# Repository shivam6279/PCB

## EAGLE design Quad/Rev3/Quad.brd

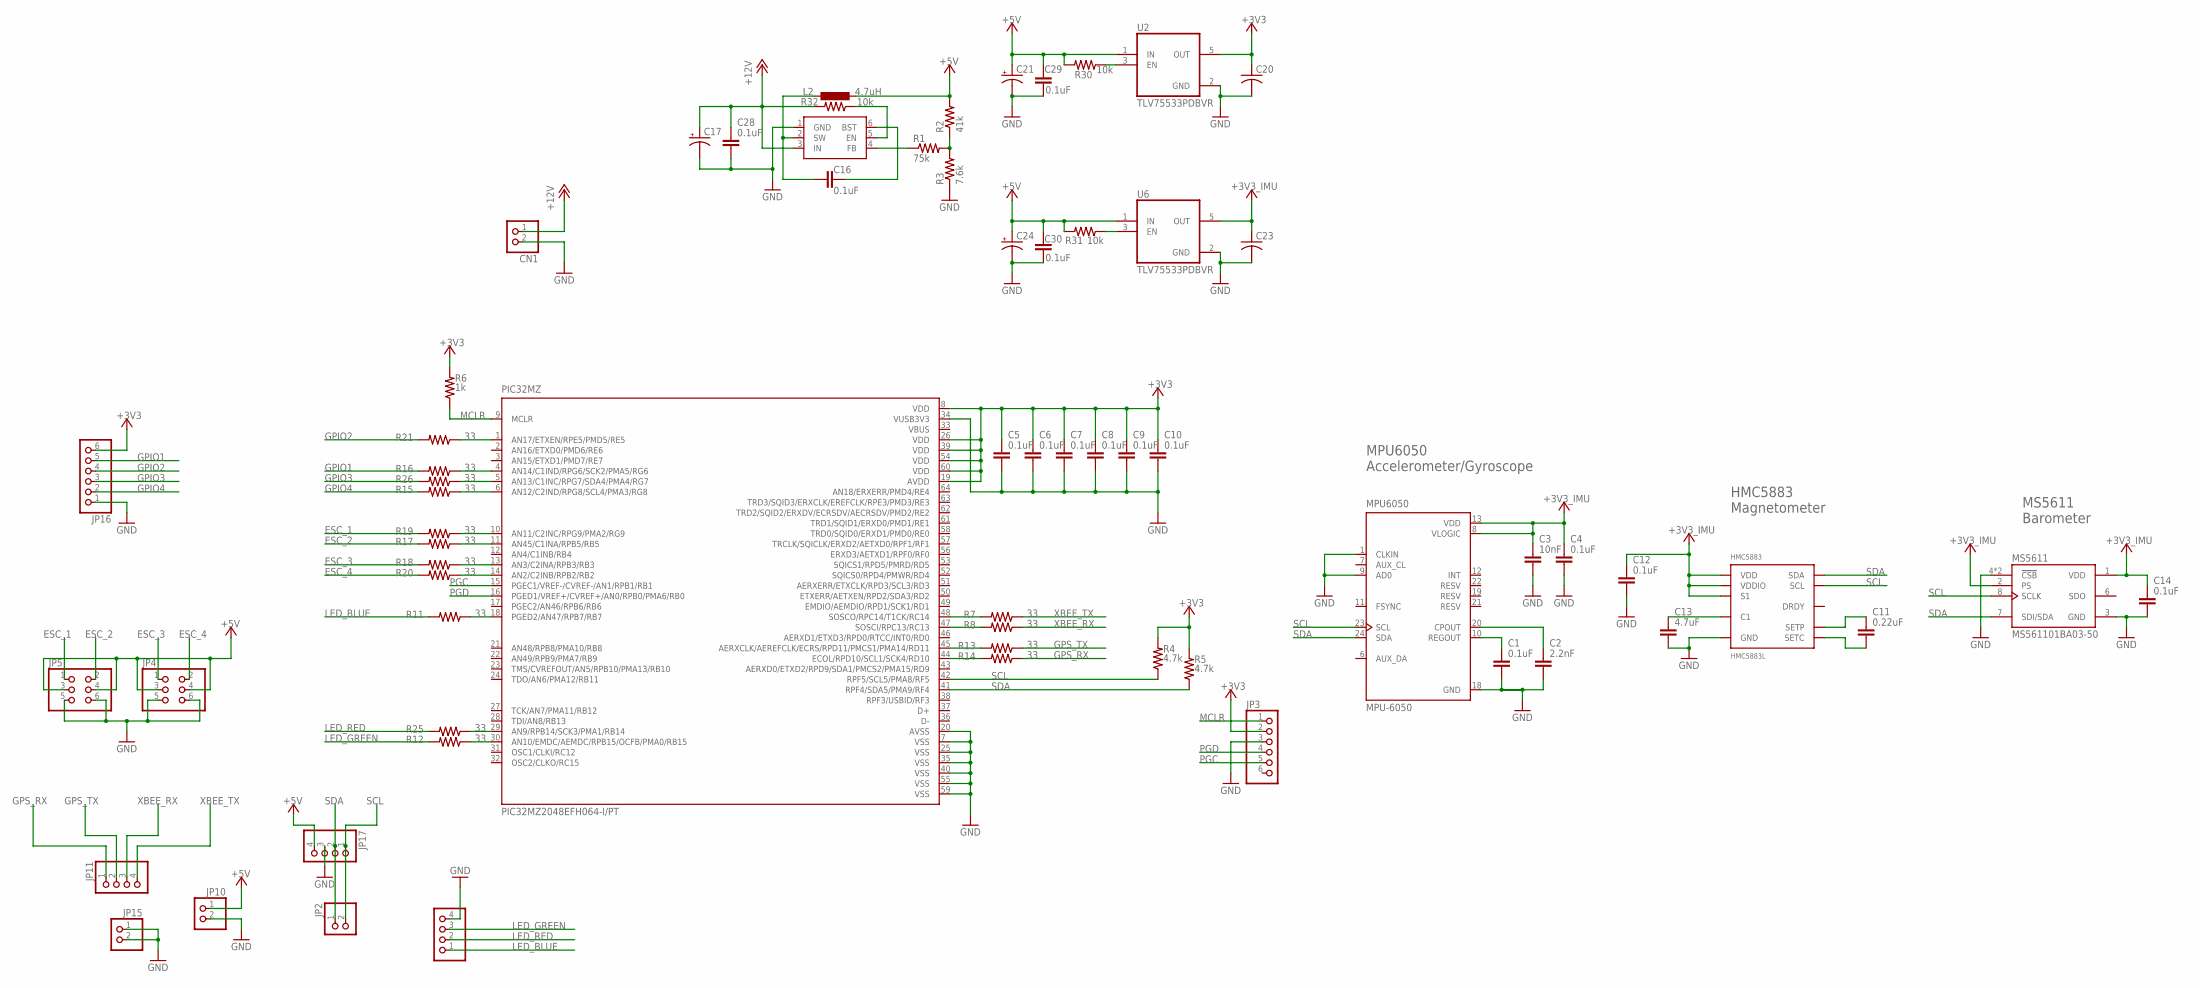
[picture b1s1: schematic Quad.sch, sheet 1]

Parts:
C1, C4, C5, C6, C7, C8, C9, C10, C12, C14, C16, C28, C29, C30: 0.1uF; C0603
C2: 2.2nF; C0603
C3: 10nF; C0603
C11: 0.22uF; C0603
C13: 4.7uF; C0603
C17: CPOL-USC/6032-28R; C/6032-28R
C20, C23: C-USC0805; C0805
C21, C24: CPOL-USB/3528-21W; B/3528-21W
CN1: JST_2PIN-THM-RA; JST-PH-2-THM-RA
HMC5883: HMC5883L; LPCC-16
JP2, JP10, JP15: PINHD-1X2; 1X02
JP3: PINHD-1X6/90; 1X06/90
JP4, JP5: PINHD-2X3; 2X03
JP9, JP11: PINHD-1X4; 1X04
JP16: PINHD-1X6; 1X06
JP17: PINHD-1X4/90; 1X04/90
L2: 4.7uH; L2825P
MPU6050: MPU-6050; QFN50P400X400X95-24N
MS5611: MS561101BA03-50; SON125P500X300X100-8N
PIC32MZ: PIC32MZ2048EFH064-I/PT; QFP50P1200X1200X120-64N
R1: 75k; R0603
R2: 41k; R0603
R3: 7.6k; R0603
R4, R5: 4.7k; R0603
R6: 1k; R0603
R7, R8, R11, R12, R13, R14, R15, R16, R17, R18, R19, R20, R21, R25, R26: 33; R0603
R30, R31, R32: 10k; R0603
U2, U6: TLV75533PDBVR; SOT95P280X145-5N
U$2: AP65211A; SOT95P280X140-6N

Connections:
+3V3: C5.1, C6.1, C7.1, C8.1, C9.1, C10.1, C20.1, JP3.2, JP16.6, PIC32MZ.8 (VDD), PIC32MZ.19 (AVDD), PIC32MZ.26 (VDD), PIC32MZ.39 (VDD), PIC32MZ.54 (VDD), PIC32MZ.60 (VDD), R4.2, R5.2, R6.2, U2.5 (OUT)
+5V: C21.+, C24.+, C29.1, C30.1, JP4.3, JP4.4, JP5.3, JP5.4, JP10.1, JP17.4, L2.1, R2.2, R30.2, R31.2, U2.1 (IN), U6.1 (IN)
+12V: C17.+, C28.1, CN1.1 (2), R32.2, U$2.3 (IN)
ESC_1: JP5.1, R19.2
ESC_2: JP5.2, R17.2
ESC_3: JP4.1, R18.2
ESC_4: JP4.2, R20.2
GND: C1.2, C2.2, C3.2, C4.2, C5.2, C6.2, C7.2, C8.2, C9.2, C10.2, C12.2, C13.2, C14.2, C17.-, C20.2, C21.-, C23.2, C24.-, C28.2, C29.2, C30.2, CN1.2 (1), HMC5883.9 (GND), HMC5883.11 (GND), JP3.3, JP4.5, JP4.6, JP5.5, JP5.6, JP9.4, JP10.2, JP15.1, JP15.2, JP16.1, JP17.3, MPU6050.1 (CLKIN), MPU6050.9 (AD0), MPU6050.18 (GND), MS5611.3 (GND), MS5611.4 (!CSB), MS5611.5 (!CSB), PIC32MZ.7 (VSS), PIC32MZ.20 (AVSS), PIC32MZ.25 (VSS), PIC32MZ.34 (VUSB3V3), PIC32MZ.35 (VSS), PIC32MZ.40 (VSS), PIC32MZ.55 (VSS), PIC32MZ.59 (VSS), R3.1, U2.2 (GND), U6.2 (GND), U$2.1 (GND)
GPIO1: JP16.5, R16.2
GPIO2: JP16.4, R21.2
GPIO3: JP16.3, R26.2
GPIO4: JP16.2, R15.2
GPS_RX: JP11.1, R14.1
GPS_TX: JP11.2, R13.1
LED_BLUE: JP9.1, R11.2
LED_GREEN: JP9.3, R12.2
LED_RED: JP9.2, R25.2
MCLR: JP3.1, PIC32MZ.9 (MCLR), R6.1
unnamed: C1.1, MPU6050.10 (REGOUT)
unnamed: C2.1, MPU6050.20 (CPOUT)
unnamed: C11.1, HMC5883.8 (SETP)
unnamed: C11.2, HMC5883.12 (SETC)
unnamed: C13.1, HMC5883.10 (C1)
unnamed: C16.1, L2.2, U$2.2 (SW)
unnamed: C16.2, U$2.6 (BST)
unnamed: R1.1, U$2.4 (FB)
unnamed: R1.2, R2.1, R3.2
unnamed: PIC32MZ.48 (SOSCO/RPC14/T1CK/RC14), R7.2
unnamed: PIC32MZ.47 (SOSCI/RPC13/RC13), R8.2
unnamed: PIC32MZ.18 (PGED2/AN47/RPB7/RB7), R11.1
unnamed: PIC32MZ.45 (AERXCLK/AEREFCLK/ECRS/RPD11/PMCS1/PMA14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), R13.2
unnamed: PIC32MZ.44 (ECOL/RPD10/SCL1/SCK4/RD10), R14.2
unnamed: PIC32MZ.29 (AN9/RPB14/SCK3/PMA1/RB14), R25.1
unnamed: PIC32MZ.4 (AN14/C1IND/RPG6/SCK2/PMA5/RG6), R16.1
unnamed: PIC32MZ.1 (AN17/ETXEN/RPE5/PMD5/RE5), R21.1
unnamed: PIC32MZ.11 (AN45/C1INA/RPB5/RB5), R17.1
unnamed: PIC32MZ.13 (AN3/C2INA/RPB3/RB3), R18.1
unnamed: PIC32MZ.10 (AN11/C2INC/RPG9/PMA2/RG9), R19.1
unnamed: PIC32MZ.14 (AN2/C2INB/RPB2/RB2), R20.1
unnamed: PIC32MZ.5 (AN13/C1INC/RPG7/SDA4/PMA4/RG7), R26.1
unnamed: PIC32MZ.6 (AN12/C2IND/RPG8/SCL4/PMA3/RG8), R15.1
unnamed: R31.1, U6.3 (EN)
unnamed: R30.1, U2.3 (EN)
unnamed: PIC32MZ.30 (AN10/EMDC/AEMDC/RPB15/OCFB/PMA0/RB15), R12.1
unnamed: R32.1, U$2.5 (EN)
PGC: JP3.5, PIC32MZ.15 (PGEC1/VREF-/CVREF-/AN1/RPB1/RB1)
PGD: JP3.4, PIC32MZ.16 (PGED1/VREF+/CVREF+/AN0/RPB0/PMA6/RB0)
SCL: HMC5883.1 (SCL), JP2.2, JP17.1, MPU6050.23 (SCL), MS5611.8 (SCLK), PIC32MZ.42 (RPF5/SCL5/PMA8/RF5), R4.1
SDA: HMC5883.16 (SDA), JP2.1, JP17.2, MPU6050.24 (SDA), MS5611.7 (SDI/SDA), PIC32MZ.41 (RPF4/SDA5/PMA9/RF4), R5.1
VBUS: PIC32MZ.33 (VBUS)
VCC: C3.1, C4.1, C12.1, C14.1, C23.1, HMC5883.2 (VDD), HMC5883.4 (S1), HMC5883.13 (VDDIO), MPU6050.8 (VLOGIC), MPU6050.13 (VDD), MS5611.1 (VDD), MS5611.2 (PS), U6.5 (OUT)
XBEE_RX: JP11.3, R8.1
XBEE_TX: JP11.4, R7.1

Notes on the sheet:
MPU6050 Accelerometer/Gyroscope
HMC5883 Magnetometer
MS5611 Barometer

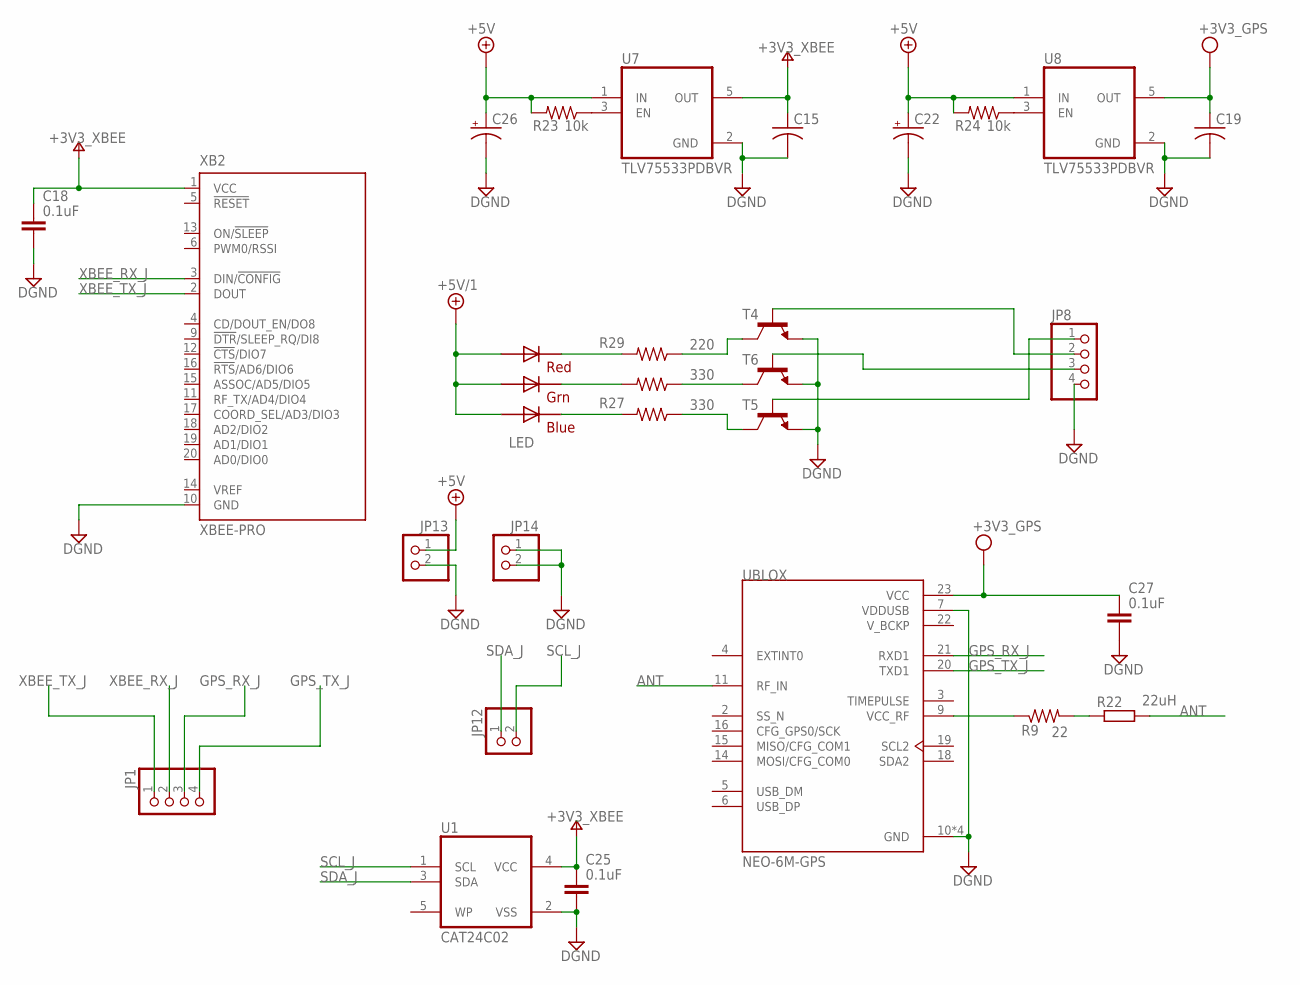
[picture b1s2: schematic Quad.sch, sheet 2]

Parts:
C15, C19: C-USC0805; C0805
C18, C25, C27: 0.1uF; C0603
C22, C26: CPOL-USB/3528-21W; B/3528-21W
JP1, JP8: PINHD-1X4; 1X04
JP12, JP13, JP14: PINHD-1X2; 1X02
LED: RGBLED5050
R9: 22; R0603
R22: 22uH; R0805
R23, R24: 10k; R0603
R27, R28: 330; R0603
R29: 220; R0603
T4, T5, T6: -NPN-SOT23-EBC; SOT23-EBC
U1: CAT24C02; SOT95P280X145-5N
U7, U8: TLV75533PDBVR; SOT95P280X145-5N
UBLOX: NEO-6M-GPS; XCVR_NEO-6M-GPS
XB2: XBEE-PRO

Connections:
+5V/1: C22.+, C26.+, JP13.1, LED.1 (GREEN_A), LED.2 (RED_A), LED.3 (BLUE_A), R23.2, R24.2, U7.1 (IN), U8.1 (IN)
ANT: R22.2, UBLOX.11 (RF_IN)
DGND: C15.2, C18.2, C19.2, C22.-, C25.2, C26.-, C27.2, JP8.4, JP13.2, JP14.1, JP14.2, T4.E, T5.E, T6.E, U1.2 (VSS), U7.2 (GND), U8.2 (GND), UBLOX.7 (VDDUSB), UBLOX.10 (GND), UBLOX.12 (GND), UBLOX.13 (GND), UBLOX.24 (GND), XB2.10 (GND)
GPS_RX_J: JP1.3, UBLOX.21 (RXD1)
GPS_TX_J: JP1.4, UBLOX.20 (TXD1)
LED_BLUE1: JP8.1, T5.B
LED_GREEN1: JP8.2, T4.B
unnamed: LED.5 (RED_C), R29.2
unnamed: LED.6 (GREEN_C), R28.2
unnamed: R9.2, R22.1
unnamed: LED.4 (BLUE_C), R27.2
unnamed: R9.1, UBLOX.9 (VCC_RF)
unnamed: R23.1, U7.3 (EN)
unnamed: R24.1, U8.3 (EN)
unnamed: JP8.3, T6.B
unnamed: R28.1, T6.C
unnamed: R29.1, T4.C
unnamed: R27.1, T5.C
SCL_J: JP12.2, U1.1 (SCL)
SDA_J: JP12.1, U1.3 (SDA)
V+: C15.1, C18.1, C25.1, U1.4 (VCC), U7.5 (OUT), XB2.1 (VCC)
VDD: C19.1, C27.1, U8.5 (OUT), UBLOX.23 (VCC)
V_BCKP: UBLOX.22 (V_BCKP)
XBEE_RX_J: JP1.2, XB2.3 (DIN/!CONFIG)
XBEE_TX_J: JP1.1, XB2.2 (DOUT)

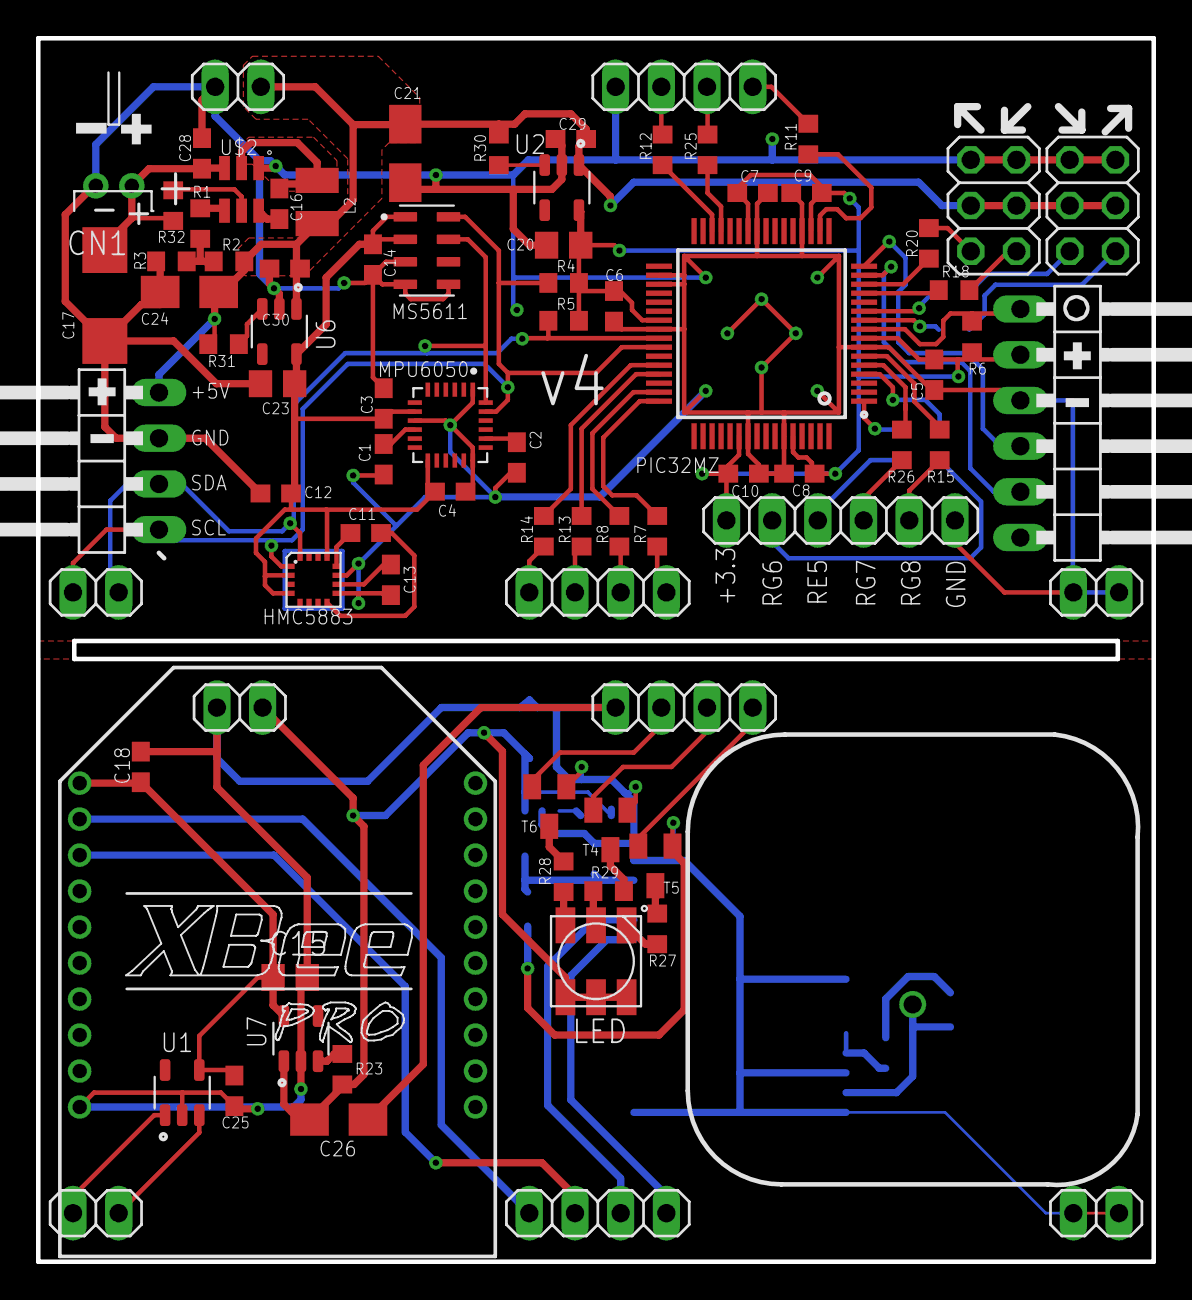
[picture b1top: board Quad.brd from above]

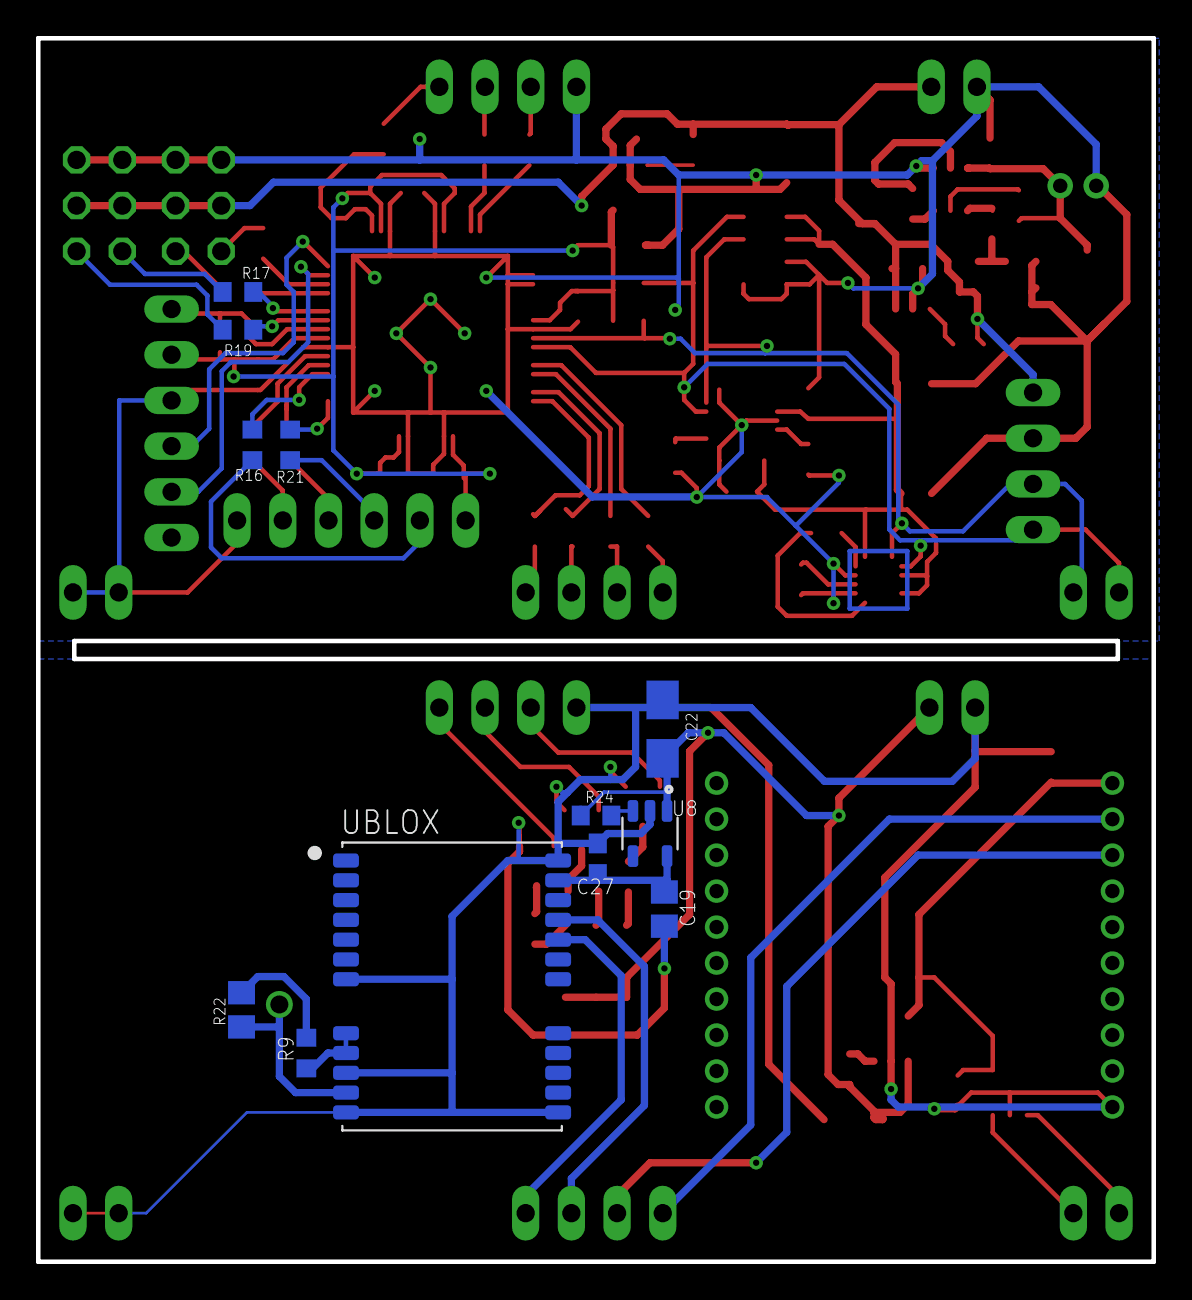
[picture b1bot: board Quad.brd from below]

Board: 2 copper layers, 62.0 x 68.0 mm, 94 parts (12 on the bottom side), 76 nets.

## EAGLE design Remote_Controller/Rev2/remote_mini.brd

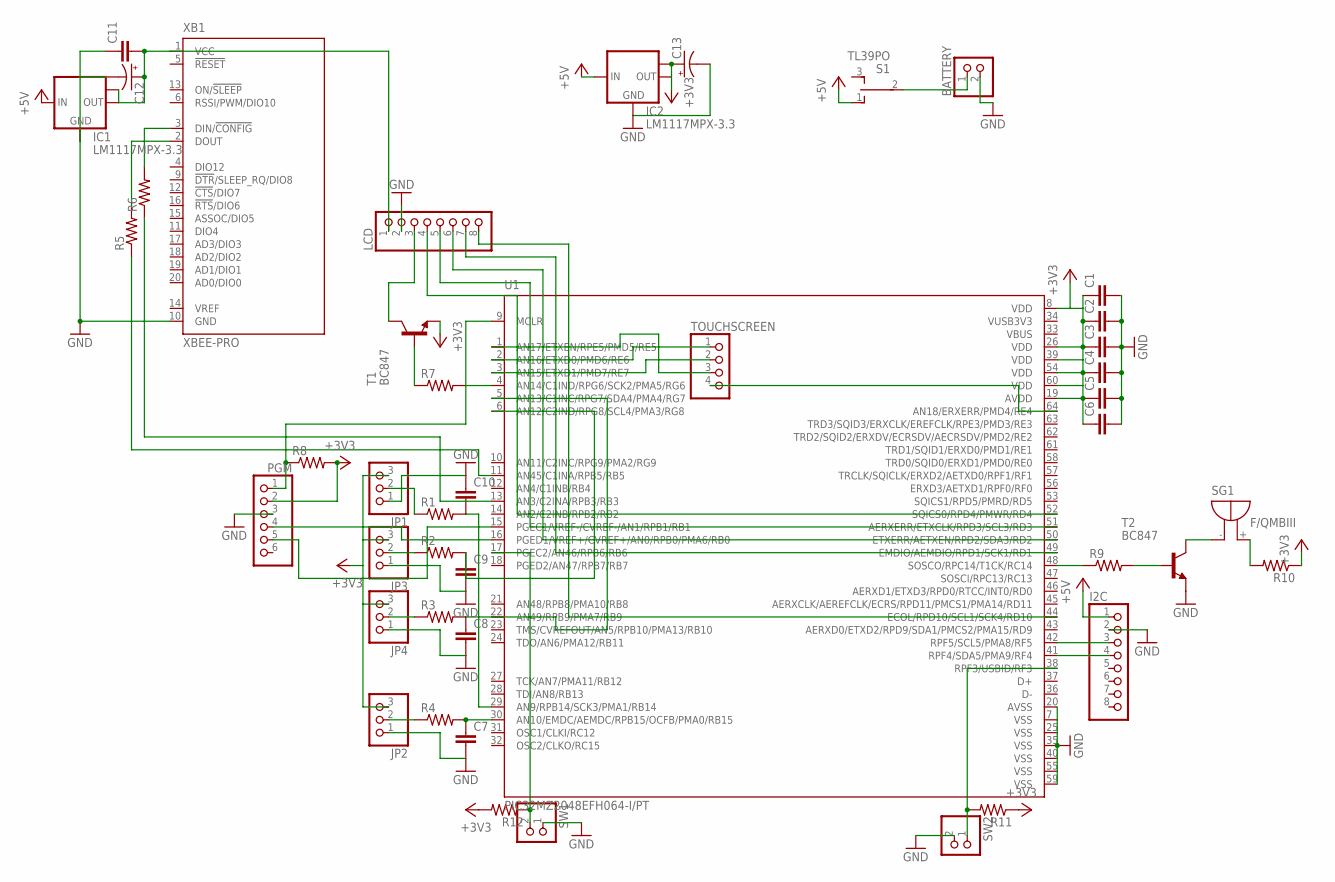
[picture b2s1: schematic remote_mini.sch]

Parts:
BATTERY: PINHD-1X2; 1X02
C1, C2, C3, C4, C5, C6, C11: C-EUC0603; C0603
C7, C8, C9, C10: C-EUC0805; C0805
C12, C13: CPOL-USCT7343; CT7343
I2C: PINHD-1X8; 1X08
IC1, IC2: LM1117MPX-3.3; SOT223
JP1, JP2, JP3, JP4: PINHD-1X3; 1X03
LCD: PINHD-1X8; 1X08
PGM: PINHD-1X6; 1X06
R1, R2, R3, R4, R5, R6, R7, R8, R9, R10, R11, R12: R-US_R0603; R0603
S1: TL39PO; TL3XPO
SG1: F/QMBIII
SW1, SW2: PINHD-1X2; 1X02
T1, T2: BC847; SOT23
TOUCHSCREEN: PINHD-1X4; 1X04
U1: PIC32MZ2048EFH064-I/PT; QFP50P1200X1200X120-64N
XB1: XBEE-PRO

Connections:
+3V3: C1.1, C2.1, C3.1, C4.1, C5.1, C6.1, C13.+, IC2.2 (OUT), IC2.TAB (OUT1), JP1.3, JP2.3, JP3.3, JP4.3, PGM.2, R8.2, R10.1, R11.1, R12.2, T1.2 (E), U1.8 (VDD), U1.19 (AVDD), U1.26 (VDD), U1.39 (VDD), U1.54 (VDD), U1.60 (VDD)
+5V: I2C.1, IC1.3 (IN), IC2.3 (IN), S1.1 (O)
GND: BATTERY.2, C1.2, C2.2, C3.2, C4.2, C5.2, C6.2, C7.2, C8.2, C9.2, C10.1, C11.1, C12.-, C13.-, I2C.2, IC1.1 (GND), IC2.1 (GND), JP1.1, JP2.1, JP3.1, JP4.1, LCD.2, PGM.3, SW1.1, SW2.2, T2.2 (E), U1.7 (VSS), U1.20 (AVSS), U1.25 (VSS), U1.35 (VSS), U1.40 (VSS), U1.55 (VSS), U1.59 (VSS), XB1.10 (GND)
unnamed: R9.1, U1.48 (SOSCO/RPC14/T1CK/RC14)
unnamed: C7.1, R4.2, U1.30 (AN10/EMDC/AEMDC/RPB15/OCFB/PMA0/RB15)
unnamed: JP2.2, R4.1
unnamed: C11.2, C12.+, IC1.2 (OUT), IC1.TAB (OUT1), LCD.1, XB1.1 (VCC)
unnamed: LCD.6, U1.50 (ETXERR/AETXEN/RPD2/SDA3/RD2)
unnamed: R5.1, U1.11 (AN45/C1INA/RPB5/RB5)
unnamed: R5.2, XB1.2 (DOUT)
unnamed: R6.1, U1.13 (AN3/C2INA/RPB3/RB3)
unnamed: R6.2, XB1.3 (DIN/!CONFIG)
unnamed: C10.2, R1.2, U1.29 (AN9/RPB14/SCK3/PMA1/RB14)
unnamed: JP4.2, R3.1
unnamed: C8.1, R3.2, U1.5 (AN13/C1INC/RPG7/SDA4/PMA4/RG7)
unnamed: JP3.2, R2.1
unnamed: JP1.2, R1.1
unnamed: LCD.5, U1.51 (AERXERR/ETXCLK/RPD3/SCL3/RD3)
unnamed: LCD.4, U1.52 (SQICS0/RPD4/PMWR/RD4)
unnamed: LCD.7, U1.49 (EMDIO/AEMDIO/RPD1/SCK1/RD1)
unnamed: LCD.8, U1.44 (ECOL/RPD10/SCL1/SCK4/RD10)
unnamed: R7.2, U1.4 (AN14/C1IND/RPG6/SCK2/PMA5/RG6)
unnamed: R7.1, T1.1 (B)
unnamed: LCD.3, T1.3 (C)
unnamed: BATTERY.1, S1.2
unnamed: I2C.3, U1.42 (RPF5/SCL5/PMA8/RF5)
unnamed: I2C.4, U1.41 (RPF4/SDA5/PMA9/RF4)
unnamed: PGM.1, R8.1, U1.9 (MCLR)
unnamed: PGM.4, U1.16 (PGED1/VREF+/CVREF+/AN0/RPB0/PMA6/RB0)
unnamed: PGM.5, U1.15 (PGEC1/VREF-/CVREF-/AN1/RPB1/RB1)
unnamed: R9.2, T2.1 (B)
unnamed: C9.1, R2.2, U1.6 (AN12/C2IND/RPG8/SCL4/PMA3/RG8)
unnamed: SG1.- (+), T2.3 (C)
unnamed: R10.2, SG1.+ (-)
unnamed: R11.2, SW2.1, U1.38 (RPF3/USBID/RF3)
unnamed: R12.1, SW1.2, U1.17 (PGEC2/AN46/RPB6/RB6)
unnamed: TOUCHSCREEN.3, U1.1 (AN17/ETXEN/RPE5/PMD5/RE5)
unnamed: TOUCHSCREEN.1, U1.2 (AN16/ETXD0/PMD6/RE6)
unnamed: TOUCHSCREEN.2, U1.3 (AN15/ETXD1/PMD7/RE7)
unnamed: TOUCHSCREEN.4, U1.64 (AN18/ERXERR/PMD4/RE4)
VBUS: U1.33 (VBUS)
VUSB3V3: U1.34 (VUSB3V3)

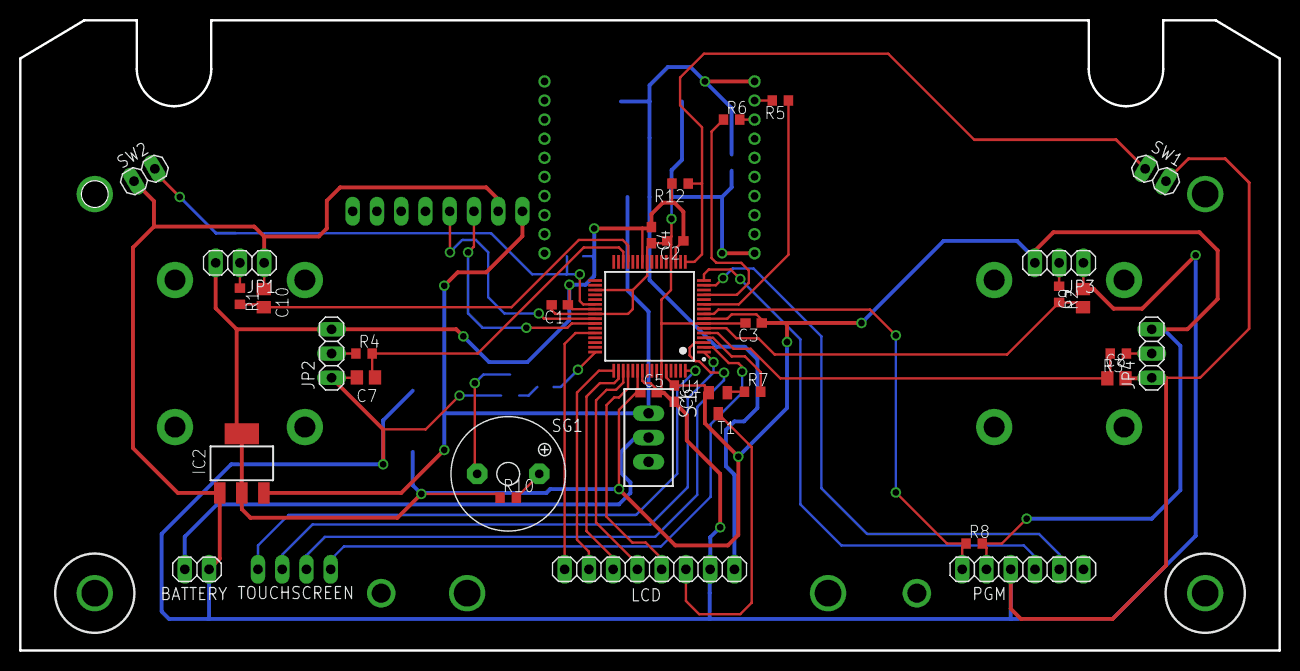
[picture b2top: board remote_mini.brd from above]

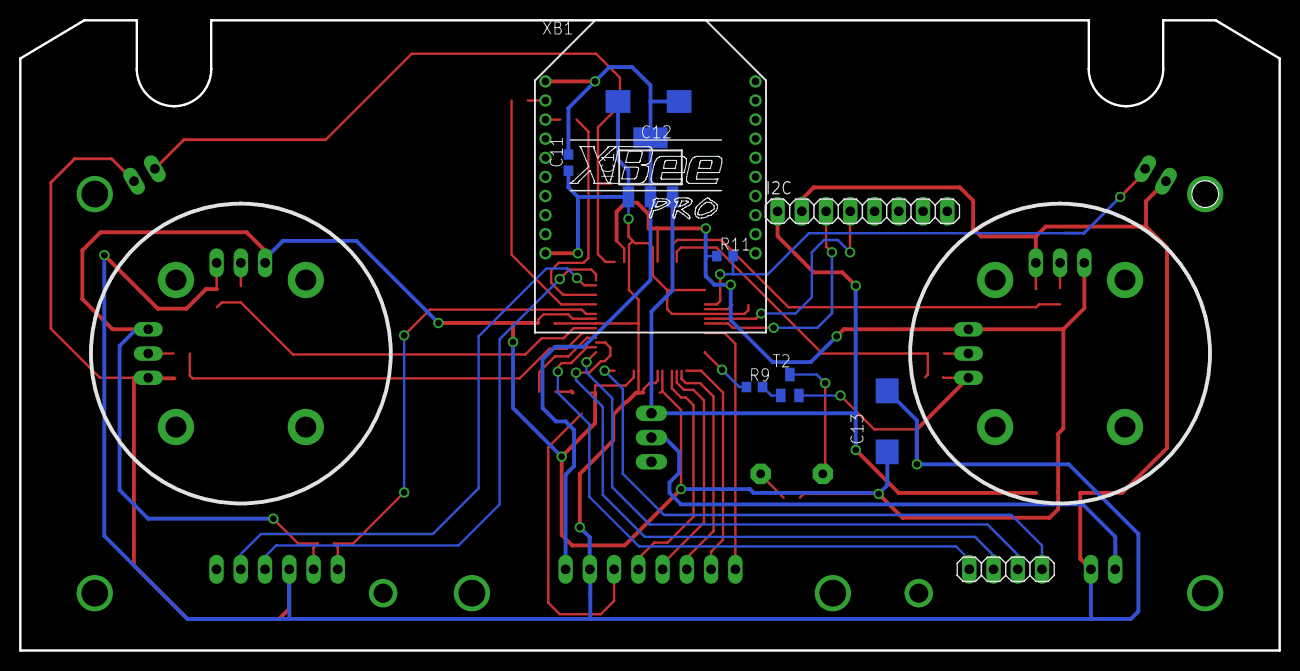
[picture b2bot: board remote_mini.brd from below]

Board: 2 copper layers, 131.9 x 66.0 mm, 44 parts (10 on the bottom side), 40 nets.

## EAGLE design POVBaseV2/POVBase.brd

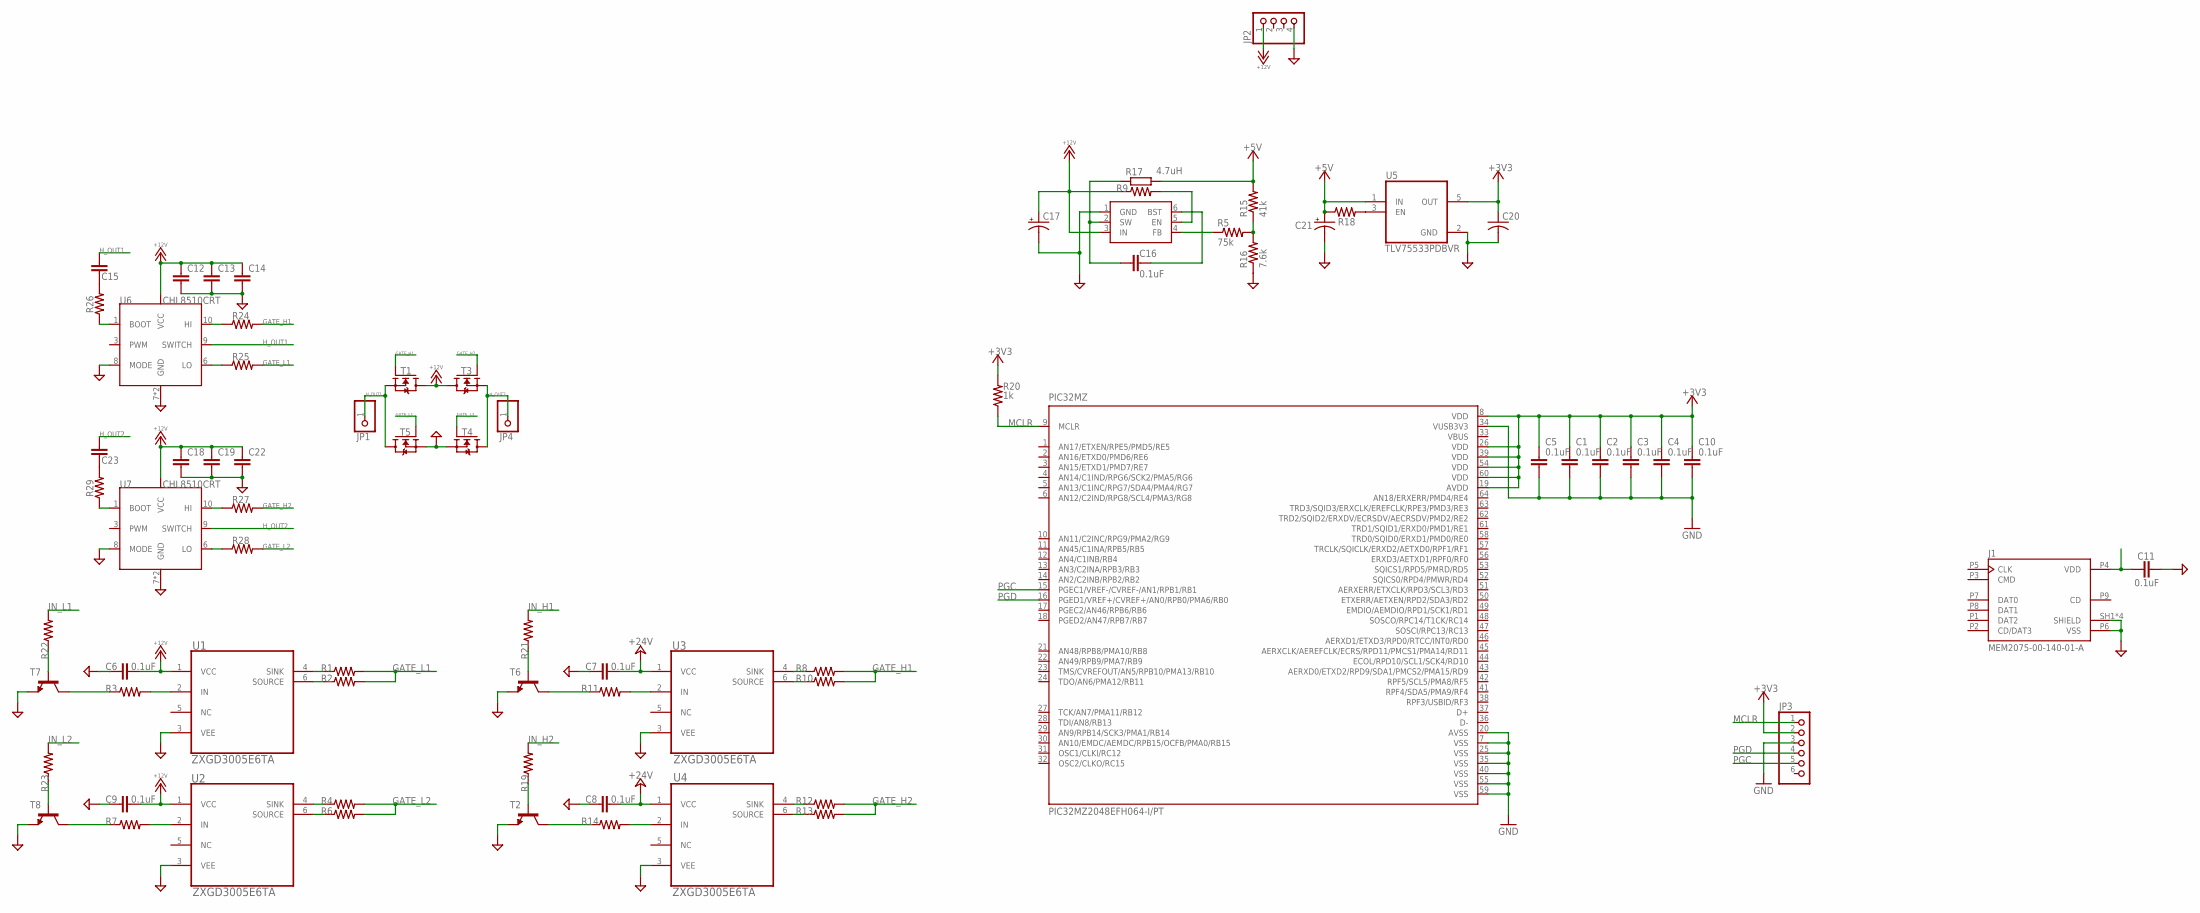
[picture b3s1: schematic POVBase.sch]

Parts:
C1, C2, C3, C4, C5, C10, C11, C16: 0.1uF; C0603
C6, C7, C8, C9: 0.1uF; C0805
C12, C13, C14, C15, C18, C19, C22, C23: C-EUC0603; C0603
C17: CPOL-USC/6032-28R; C/6032-28R
C20: C-USC0805; C0805
C21: CPOL-USB/3528-21W; B/3528-21W
J1: MEM2075-00-140-01-A; GCT_MEM2075-00-140-01-A
JP1, JP4: PINHD-1X1; 1X01
JP2: PINHD-1X4; 1X04
JP3: PINHD-1X6; 1X06
PIC32MZ: PIC32MZ2048EFH064-I/PT; QFP50P1200X1200X120-64N
R1, R2, R4, R6, R8, R10, R12, R13, R24, R25, R27, R28: R-US_R1206; R1206
R3, R7, R9, R11, R14, R18, R19, R21, R22, R23, R26, R29: R-US_R0603; R0603
R5: 75k; R0603
R15: 41k; R0603
R16: 7.6k; R0603
R17: 4.7uH; R0805
R20: 1k; R0603
T1, T3, T4, T5: MOSFET-N-D2PAK; D2PAK_TO263
T2, T6, T7, T8: -NPN-SOT23-EBC; SOT23-EBC
U1, U2, U3, U4: ZXGD3005E6TA; SOT95P280X130-6N
U5: TLV75533PDBVR; SOT95P280X145-5N
U6, U7: CHL8510CRT; 10-VFDFN
U$2: AP65211A; SOT95P280X140-6N

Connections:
+3V3: C1.1, C2.1, C3.1, C4.1, C5.1, C10.1, C20.1, JP3.2, PIC32MZ.8 (VDD), PIC32MZ.19 (AVDD), PIC32MZ.26 (VDD), PIC32MZ.39 (VDD), PIC32MZ.54 (VDD), PIC32MZ.60 (VDD), R20.2, U5.5 (OUT)
+5V: C21.+, R15.2, R17.2, R18.1, U5.1 (IN)
+12V: C6.2, C9.2, C12.1, C13.1, C14.1, C17.+, C18.1, C19.1, C22.1, JP2.1, R9.1, T1.2 (D), T3.2 (D), U1.1 (VCC), U2.1 (VCC), U6.2 (VCC), U6.4 (VCC), U6.5 (VCC), U7.2 (VCC), U7.4 (VCC), U7.5 (VCC), U$2.3 (IN)
+24V: C7.2, C8.2, U3.1 (VCC), U4.1 (VCC)
GATE_H1: R8.2, R10.2, R24.2, T1.1 (G)
GATE_H2: R12.2, R13.2, R27.2, T3.1 (G)
GATE_L1: R1.2, R2.2, R25.2, T5.1 (G)
GATE_L2: R4.2, R6.2, R28.2, T4.1 (G)
GND: C1.2, C2.2, C3.2, C4.2, C5.2, C6.1, C7.1, C8.1, C9.1, C10.2, C11.2, C12.2, C13.2, C14.2, C17.-, C18.2, C19.2, C20.2, C21.-, C22.2, J1.P6 (VSS), J1.SH1 (SHIELD), J1.SH2 (SHIELD), J1.SH3 (SHIELD), J1.SH4 (SHIELD), JP2.4, JP3.3, PIC32MZ.7 (VSS), PIC32MZ.20 (AVSS), PIC32MZ.25 (VSS), PIC32MZ.34 (VUSB3V3), PIC32MZ.35 (VSS), PIC32MZ.40 (VSS), PIC32MZ.55 (VSS), PIC32MZ.59 (VSS), R16.1, T2.E, T4.3 (S), T5.3 (S), T6.E, T7.E, T8.E, U1.3 (VEE), U2.3 (VEE), U3.3 (VEE), U4.3 (VEE), U5.2 (GND), U6.7 (GND), U6.8 (MODE), U6.11 (GND), U7.7 (GND), U7.8 (MODE), U7.11 (GND), U$2.1 (GND)
H_OUT1: C15.1, JP1.1, T1.3 (S), T5.2 (D), U6.9 (SWITCH)
H_OUT2: C23.1, JP4.1, T3.3 (S), T4.2 (D), U7.9 (SWITCH)
IN_H1: R21.2
IN_H1_R: R11.1, T6.C
IN_H2: R19.2
IN_H2_R: R14.1, T2.C
IN_L1: R22.2
IN_L1_R: R3.1, T7.C
IN_L2: R23.2
IN_L2_R: R7.1, T8.C
MCLR: JP3.1, PIC32MZ.9 (MCLR), R20.1
unnamed: R3.2, U1.2 (IN)
unnamed: R1.1, U1.4 (SINK)
unnamed: R2.1, U1.6 (SOURCE)
unnamed: R4.1, U2.4 (SINK)
unnamed: R6.1, U2.6 (SOURCE)
unnamed: R7.2, U2.2 (IN)
unnamed: R8.1, U3.4 (SINK)
unnamed: R10.1, U3.6 (SOURCE)
unnamed: R11.2, U3.2 (IN)
unnamed: R12.1, U4.4 (SINK)
unnamed: R13.1, U4.6 (SOURCE)
unnamed: R9.2, U$2.5 (EN)
unnamed: R18.2, U5.3 (EN)
unnamed: R19.1, T2.B
unnamed: R21.1, T6.B
unnamed: C16.1, R17.1, U$2.2 (SW)
unnamed: C16.2, U$2.6 (BST)
unnamed: R5.1, U$2.4 (FB)
unnamed: R5.2, R15.1, R16.2
unnamed: R14.2, U4.2 (IN)
unnamed: R22.1, T7.B
unnamed: R23.1, T8.B
unnamed: C11.1, J1.P4 (VDD)
unnamed: R25.1, U6.6 (LO)
unnamed: R24.1, U6.10 (HI)
unnamed: C15.2, R26.2
unnamed: R26.1, U6.1 (BOOT)
unnamed: R28.1, U7.6 (LO)
unnamed: R27.1, U7.10 (HI)
unnamed: C23.2, R29.2
unnamed: R29.1, U7.1 (BOOT)
PGC: JP3.5, PIC32MZ.15 (PGEC1/VREF-/CVREF-/AN1/RPB1/RB1)
PGD: JP3.4, PIC32MZ.16 (PGED1/VREF+/CVREF+/AN0/RPB0/PMA6/RB0)
VBUS: PIC32MZ.33 (VBUS)

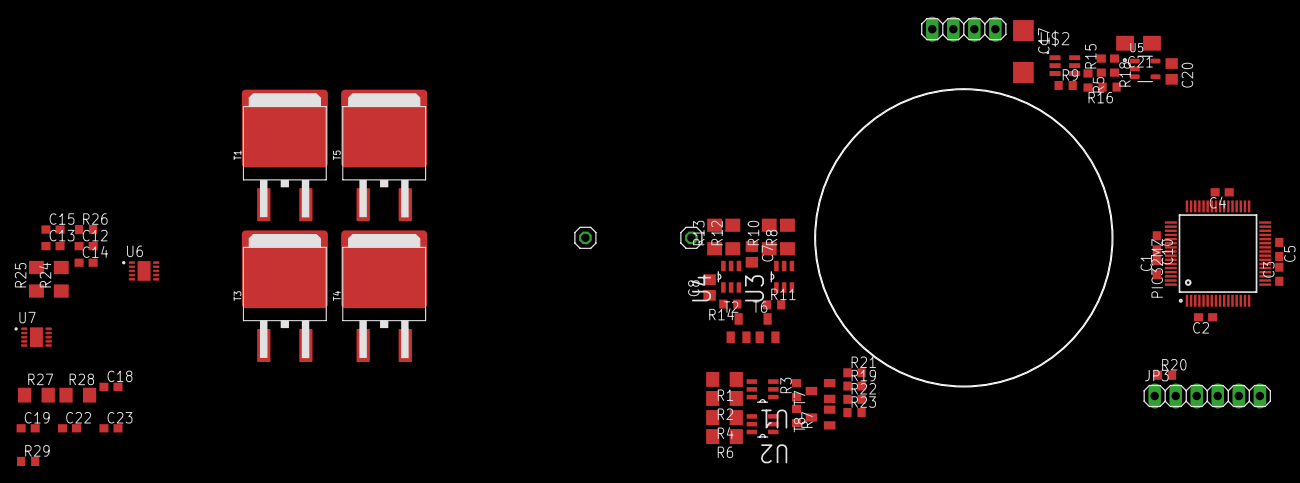
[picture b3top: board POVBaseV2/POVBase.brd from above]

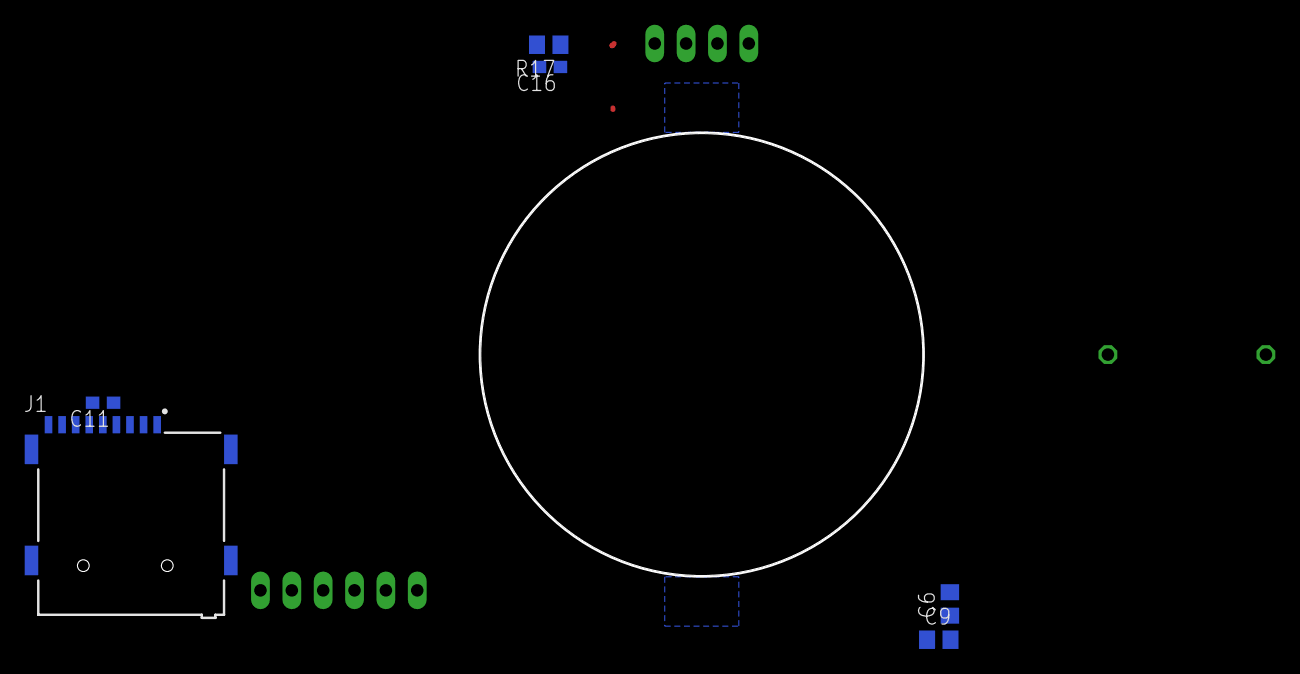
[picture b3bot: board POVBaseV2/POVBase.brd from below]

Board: 4 copper layers, 74 parts (6 on the bottom side), 49 nets.

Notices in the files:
parts and their libraries:
SparkFun-Coils: Licensing: Creative Commons ShareAlike 4.0 International - https://creativecommons.org/licenses/by-sa/4.0
